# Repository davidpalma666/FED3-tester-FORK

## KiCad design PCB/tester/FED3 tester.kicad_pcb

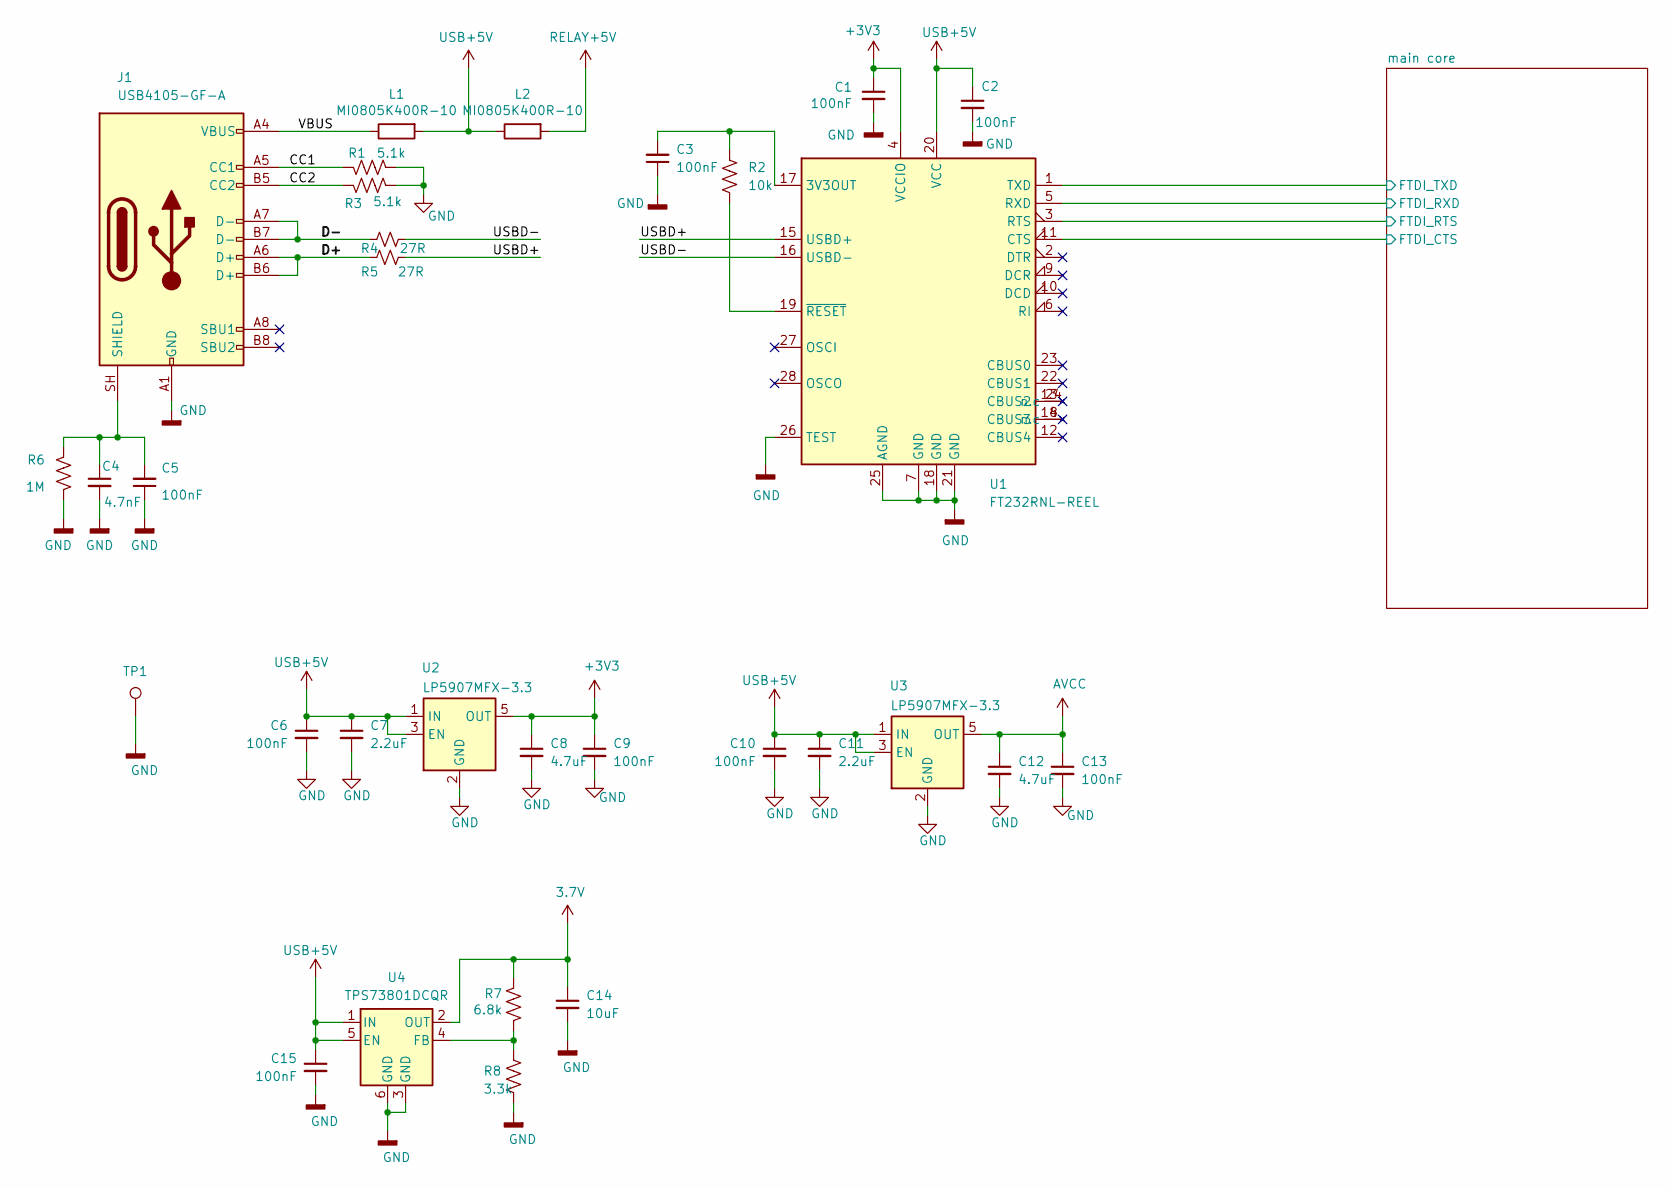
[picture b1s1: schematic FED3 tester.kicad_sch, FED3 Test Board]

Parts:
C1, C2, C3, C5, C6, C9, C10, C13, C15: 100nF; C_0402_1005Metric; Tolerance 10%; Voltage 50V; MPN CGA2B3X7R1H104K050BB
C4: 4.7nF; C_0402_1005Metric; Tolerance 10%; Voltage 100V; MPN 885012205084
C7, C11: 2.2uF; C_0603_1608Metric; Tolerance 10%; Voltage 25V; MPN GRM188R61E225KA12D
C8, C12: 4.7uF; C_0603_1608Metric; Tolerance 10%; Voltage 16V; MPN C1608X6S1C475K080AC
C14: 10uF; C_1206_3216Metric; Tolerance 10%; Voltage 25V; MPN GRM31CR71E106KA12L
J1: USB4105-GF-A; USB_C_Receptacle_GCT_USB4105-xx-A_16P_TopMnt_Horizontal; MPN USB4105-GF-A
L1, L2: MI0805K400R-10; R_0805_2012Metric; MPN MI0805K400R-10
R1, R3: 5.1k; R_0402_1005Metric; Tolerance 0.1%; MPN RT0402BRD075K1L
R2: 10k; R_0402_1005Metric; Tolerance 0.1%; MPN CPF0402B10KE1
R4, R5: 27R; R_0402_1005Metric; Tolerance 1%; MPN RMCF0402FT27R0
R6: 1M; R_0402_1005Metric; Tolerance 1%; MPN CRCW04021M00FKED
R7: 6.8k; R_0402_1005Metric; Tolerance 1%; MPN RC0402FR-076K8L
R8: 3.3k; R_0402_1005Metric; Tolerance 1%; MPN ERJ-2RKF3301X
TP1: GND; PinHeader_1x01_P2.54mm_Vertical; MPN n.a
U1: FT232RNL-REEL; SSOP-28_5.3x10.2mm_P0.65mm; MPN FT232RNL-REEL
U2, U3: LP5907MFX-3.3; SOT-23-5; MPN LP5907MFX-3.3/NOPB
U4: TPS73801DCQR; SOT-223-6; MPN TPS73801DCQR

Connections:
3.7V: C14.1, R7.2, U4.2 (OUT); also elsewhere on the board
+3V3: C1.1, C8.1, C9.1, U1.4 (VCCIO), U2.5 (OUT); also elsewhere on the board
/CC1: J1.A5 (CC1), R1.1
/CC2: J1.B5 (CC2), R3.1
/D+: J1.A6 (D+), J1.B6 (D+), R5.2
/D-: J1.A7 (D-), J1.B7 (D-), R4.2
/USBD+: R5.1, U1.15 (USBD+)
/USBD-: R4.1, U1.16 (USBD-)
/VBUS: J1.A4 (VBUS), J1.A9 (VBUS), J1.B4 (VBUS), J1.B9 (VBUS), L1.1
/main core/FTDI_CTS: U1.11 (CTS); also elsewhere on the board
/main core/FTDI_RTS: U1.3 (RTS); also elsewhere on the board
/main core/FTDI_RXD: U1.5 (RXD); also elsewhere on the board
/main core/FTDI_TXD: U1.1 (TXD); also elsewhere on the board
AVCC: C12.1, C13.1, U3.5 (OUT); also elsewhere on the board
GND: C1.2, C2.2, C3.1, C4.2, C5.1, C6.2, C7.2, C8.2, C9.2, C10.2, C11.2, C12.2, C13.2, C14.2, C15.2, J1.A1 (GND), J1.A12 (GND), J1.B1 (GND), J1.B12 (GND), R1.2, R3.2, R6.1, R8.1, TP1.1 (1_1), U1.7 (GND), U1.18 (GND), U1.21 (GND), U1.25 (AGND), U1.26 (TEST), U2.2 (GND), U3.2 (GND), U4.3 (GND), U4.6 (GND); also elsewhere on the board
unnamed: C4.1, C5.2, J1.SH (SHIELD), R6.2
unnamed: C3.2, R2.1, U1.17 (3V3OUT)
unnamed: R2.2, U1.19 (~RESET)
unnamed: R7.1, R8.2, U4.4 (FB)
RELAY+5V: L2.2; also elsewhere on the board
USB+5V: C2.1, C6.1, C7.1, C10.1, C11.1, C15.1, L1.2, L2.1, U1.20 (VCC), U2.1 (IN), U2.3 (EN), U3.1 (IN), U3.3 (EN), U4.1 (IN), U4.5 (EN); also elsewhere on the board

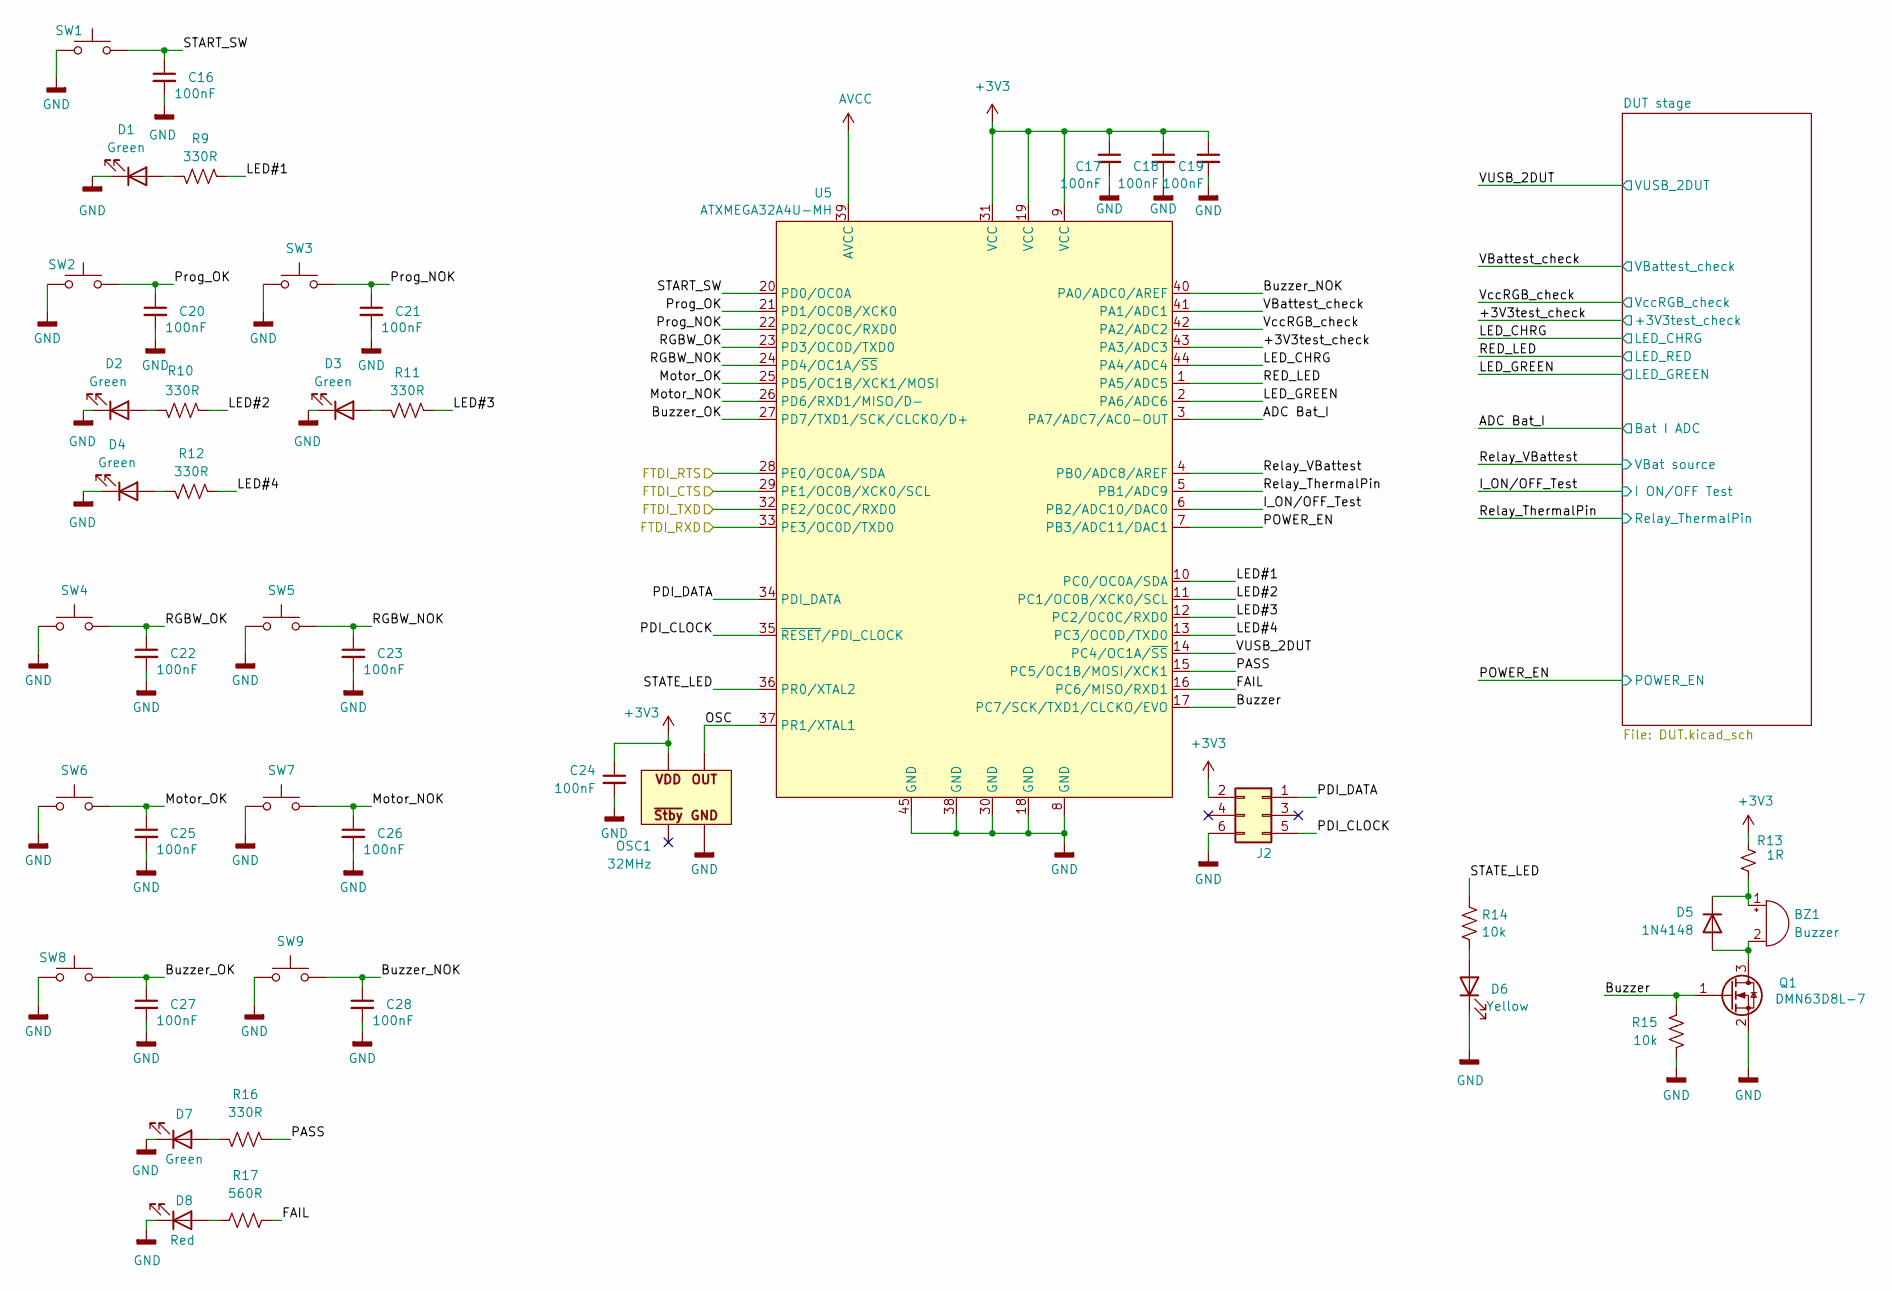
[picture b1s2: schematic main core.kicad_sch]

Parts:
BZ1: Buzzer; SMT-0540-T-9-R Buzzer; Voltage 3V; MPN CSS-0575A-SMT-TR
C16, C17, C18, C19, C20, C21, C22, C23, C24, C25, C26, C27, C28: 100nF; C_0402_1005Metric; Tolerance 10%; Voltage 50V; MPN CGA2B3X7R1H104K050BB
D1, D2, D3, D4, D7: Green; LED_0603_1608Metric; MPN LTST-C191KGKT
D5: 1N4148; D_SOD-123; MPN 1N4148WS-E3-18
D6: Yellow; LED_0603_1608Metric; MPN 5990040007F
D8: Red; LED_0603_1608Metric; MPN 5990010007F
J2: PR20203VBDN; PinHeader_2x03_P2.54mm_Vertical; MPN PR20203VBDN
OSC1: 32MHz; OSC; MPN DSC1001CI5-032.0000
Q1: DMN63D8L-7; SOT-23; MPN DMN63D8L-7
R9, R10, R11, R12, R16: 330R; R_0402_1005Metric; Tolerance 1%; MPN CRCW0402330RFKEDHP
R13: 1R; R_0402_1005Metric; Tolerance 1%; MPN CRCW04021R00FKEDC
R14, R15: 10k; R_0402_1005Metric; Tolerance 0.1%; MPN CPF0402B10KE1
R17: 560R; R_0402_1005Metric; Tolerance 1%; MPN CRCW0402560RFKED
SW1, SW2, SW3, SW4, SW5, SW6, SW7, SW8, SW9: TL3305BF260QG; SW_SPST_TL3305B; MPN TL3305BF260QG
U5: ATXMEGA32A4U-MH; QFN-44-1EP_7x7mm_P0.5mm_EP5.2x5.2mm; MPN ATXMEGA32A4U-MHR

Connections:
+3V3: C17.1, C18.1, C19.1, C24.1, J2.2, OSC1.4 (VDD), R13.1, U5.9 (VCC), U5.19 (VCC), U5.31 (VCC); also elsewhere on the board
/main core/+3V3test_check: U5.43 (PA3/ADC3); also elsewhere on the board
/main core/ADC Bat_I: U5.3 (PA7/ADC7/AC0-OUT); also elsewhere on the board
/main core/Buzzer: Q1.1 (G), R15.2, U5.17 (PC7/SCK/TXD1/CLCKO/EVO)
/main core/Buzzer_NOK: C28.1, SW9.2, U5.40 (PA0/ADC0/AREF)
/main core/Buzzer_OK: C27.1, SW8.2, U5.27 (PD7/TXD1/SCK/CLCKO/D+)
/main core/FAIL: R17.2, U5.16 (PC6/MISO/RXD1)
/main core/FTDI_CTS: U5.29 (PE1/OC0B/XCK0/SCL); also elsewhere on the board
/main core/FTDI_RTS: U5.28 (PE0/OC0A/SDA); also elsewhere on the board
/main core/FTDI_RXD: U5.33 (PE3/OC0D/TXD0); also elsewhere on the board
/main core/FTDI_TXD: U5.32 (PE2/OC0C/RXD0); also elsewhere on the board
/main core/I_ON/OFF_Test: U5.6 (PB2/ADC10/DAC0); also elsewhere on the board
/main core/LED#1: R9.2, U5.10 (PC0/OC0A/SDA)
/main core/LED#2: R10.2, U5.11 (PC1/OC0B/XCK0/SCL)
/main core/LED#3: R11.2, U5.12 (PC2/OC0C/RXD0)
/main core/LED#4: R12.2, U5.13 (PC3/OC0D/TXD0)
/main core/LED_CHRG: U5.44 (PA4/ADC4); also elsewhere on the board
/main core/LED_GREEN: U5.2 (PA6/ADC6); also elsewhere on the board
/main core/Motor_NOK: C26.1, SW7.2, U5.26 (PD6/RXD1/MISO/D-)
/main core/Motor_OK: C25.1, SW6.2, U5.25 (PD5/OC1B/XCK1/MOSI)
/main core/OSC: OSC1.3 (OUT), U5.37 (PR1/XTAL1)
/main core/PASS: R16.2, U5.15 (PC5/OC1B/MOSI/XCK1)
/main core/PDI_CLOCK: J2.5, U5.35 (~RESET/PDI_CLOCK)
/main core/PDI_DATA: J2.1, U5.34 (PDI_DATA)
/main core/POWER_EN: U5.7 (PB3/ADC11/DAC1); also elsewhere on the board
/main core/Prog_NOK: C21.1, SW3.2, U5.22 (PD2/OC0C/RXD0)
/main core/Prog_OK: C20.1, SW2.2, U5.21 (PD1/OC0B/XCK0)
/main core/RED_LED: U5.1 (PA5/ADC5); also elsewhere on the board
/main core/RGBW_NOK: C23.1, SW5.2, U5.24 (PD4/OC1A/~SS)
/main core/RGBW_OK: C22.1, SW4.2, U5.23 (PD3/OC0D/TXD0)
/main core/Relay_ThermalPin: U5.5 (PB1/ADC9); also elsewhere on the board
/main core/Relay_VBattest: U5.4 (PB0/ADC8/AREF); also elsewhere on the board
/main core/START_SW: C16.1, SW1.2, U5.20 (PD0/OC0A)
/main core/STATE_LED: R14.2, U5.36 (PR0/XTAL2)
/main core/VBattest_check: U5.41 (PA1/ADC1); also elsewhere on the board
/main core/VUSB_2DUT: U5.14 (PC4/OC1A/~SS); also elsewhere on the board
/main core/VccRGB_check: U5.42 (PA2/ADC2); also elsewhere on the board
AVCC: U5.39 (AVCC); also elsewhere on the board
GND: C16.2, C17.2, C18.2, C19.2, C20.2, C21.2, C22.2, C23.2, C24.2, C25.2, C26.2, C27.2, C28.2, D1.1 (K), D2.1 (K), D3.1 (K), D4.1 (K), D6.1 (K), D7.1 (K), D8.1 (K), J2.6, OSC1.2 (GND), Q1.2 (S), R15.1, SW1.1, SW2.1, SW3.1, SW4.1, SW5.1, SW6.1, SW7.1, SW8.1, SW9.1, U5.8 (GND), U5.18 (GND), U5.30 (GND), U5.38 (GND), U5.45 (GND); also elsewhere on the board
unnamed: BZ1.1 (+), D5.1 (K), R13.2
unnamed: BZ1.2 (-), D5.2 (A), Q1.3 (D)
unnamed: D1.2 (A), R9.1
unnamed: D2.2 (A), R10.1
unnamed: D3.2 (A), R11.1
unnamed: D4.2 (A), R12.1
unnamed: D6.2 (A), R14.1
unnamed: D7.2 (A), R16.1
unnamed: D8.2 (A), R17.1

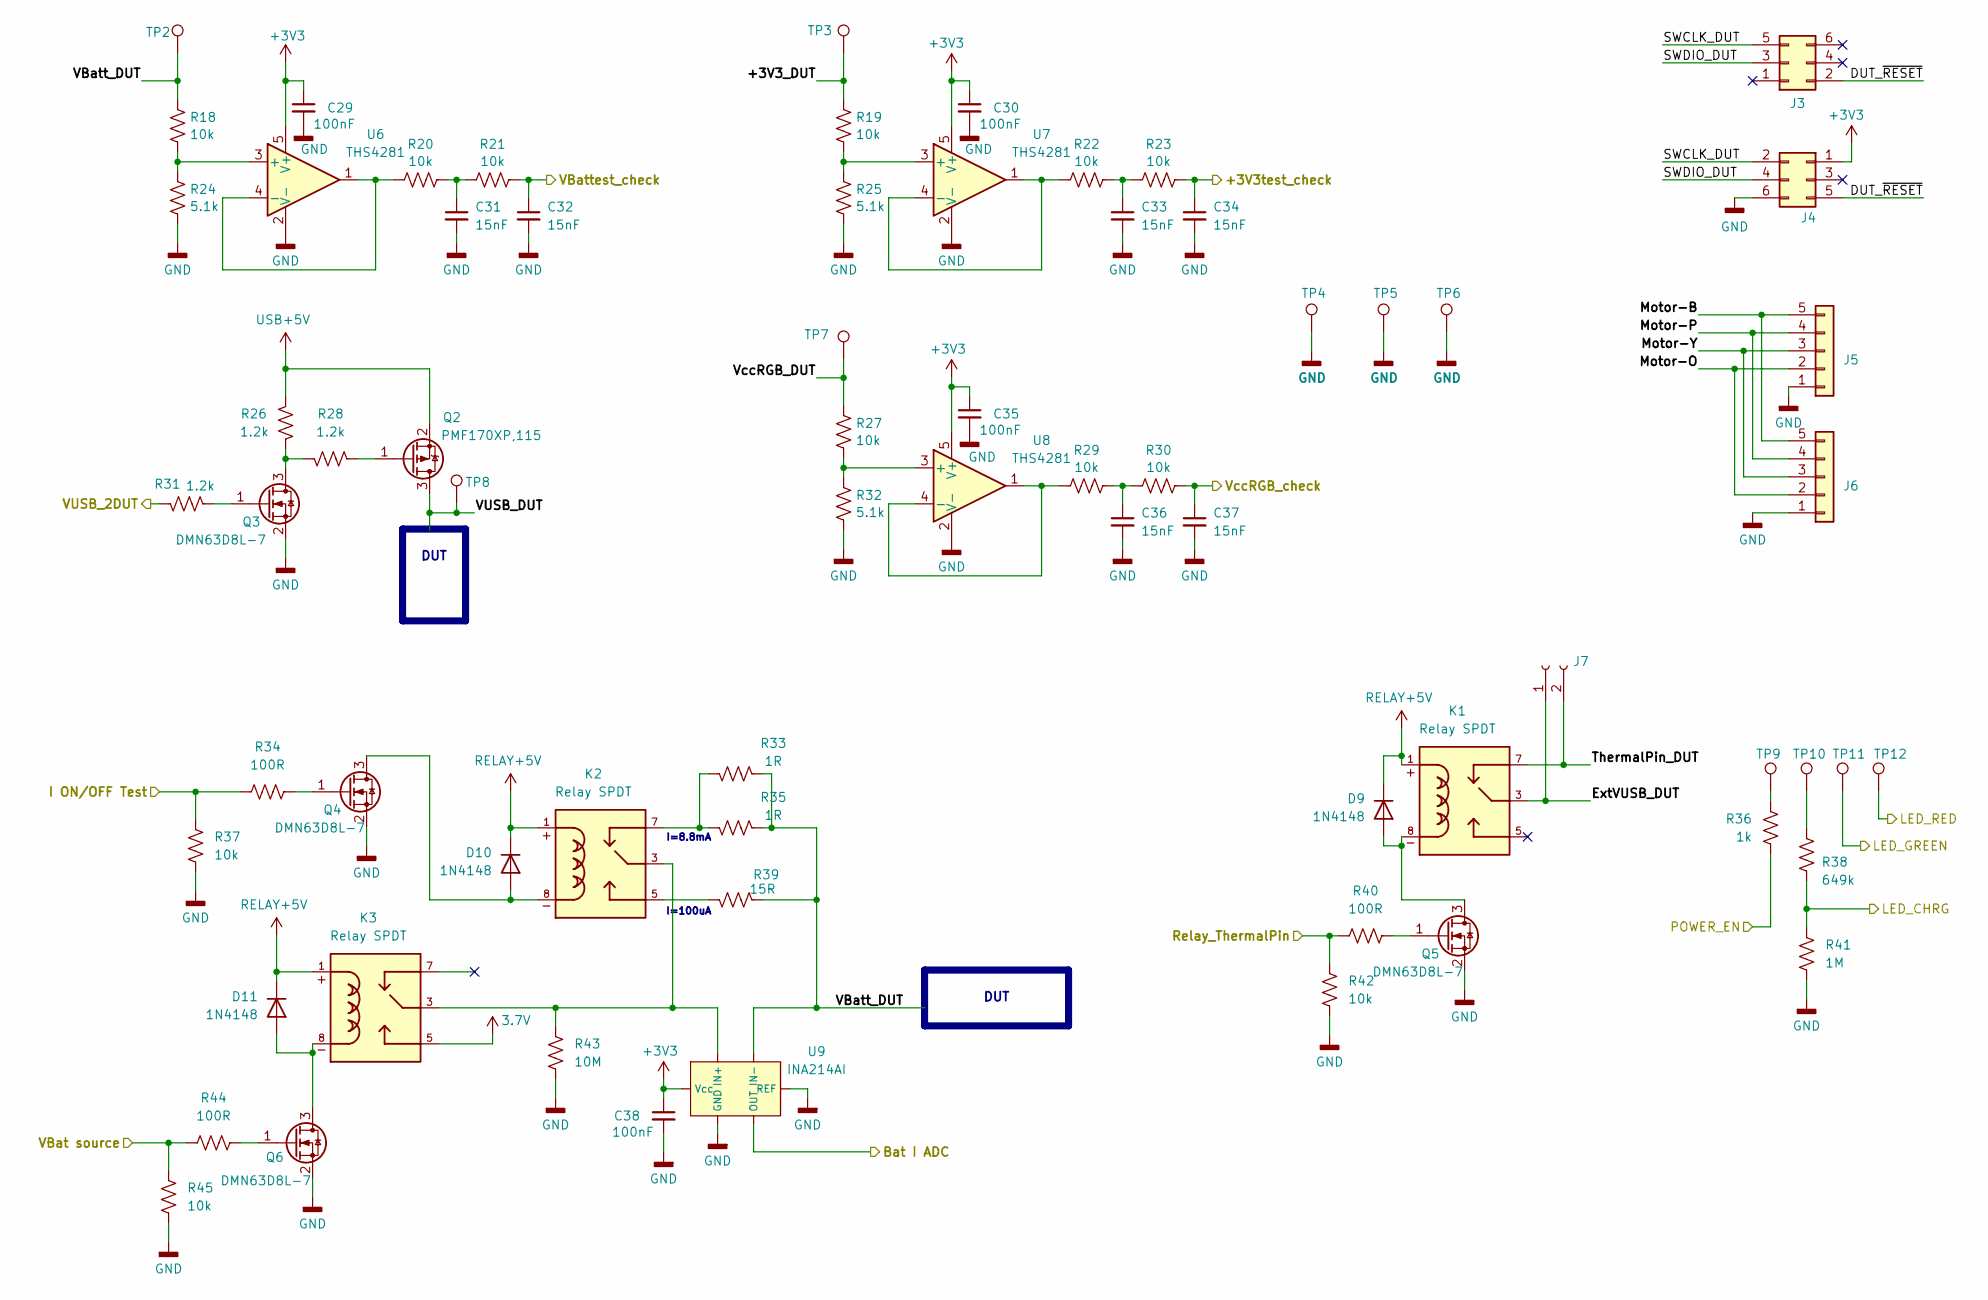
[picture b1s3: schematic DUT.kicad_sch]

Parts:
C29, C30, C35, C38: 100nF; C_0402_1005Metric; Tolerance 10%; Voltage 50V; MPN CGA2B3X7R1H104K050BB
C31, C32, C33, C34, C36, C37: 15nF; C_0402_1005Metric; Tolerance 10%; Voltage 35V; MPN CGA2B3X7R1V153K050BB
D9, D10, D11: 1N4148; D_SOD-123; MPN 1N4148WS-E3-18
J3: 6pin_hd; PinHeader_2x03_to Probes; MPN n.a
J4: 61300621021; PinHeader_2x03_P2.54mm_Horizontal; MPN 61300621021
J5: PPTC051LFBN-RC; PinSocket_1x05_P2.54mm_Vertical; MPN PPTC051LFBN-RC
J6: 61300511021; PinSocket_1x05_P2.54mm_Horizontal; MPN 61300511021
J7: PPTC021LFBN-RC; PinSocket_1x02_P2.54mm_Vertical; MPN PPTC021LFBN-RC
K1, K2, K3: Relay SPDT; RELAY_1462042-8; MPN 1462042-8
Q2: PMF170XP,115; SOT-323_SC-70; MPN PMF170XP,115
Q3, Q4, Q5, Q6: DMN63D8L-7; SOT-23; MPN DMN63D8L-7
R18, R19, R20, R21, R22, R23, R27, R29, R30, R37, R42, R45: 10k; R_0402_1005Metric; Tolerance 0.1%; MPN CPF0402B10KE1
R24, R25, R32: 5.1k; R_0402_1005Metric; Tolerance 0.1%; MPN RT0402BRD075K1L
R26, R28, R31: 1.2k; R_0402_1005Metric; Tolerance 0.1%; MPN ERA-2AEB122X
R33, R35: 1R; R_0603_1608Metric; Tolerance 0.1%; MPN RT0603BRD071RL
R34, R40, R44: 100R; R_0402_1005Metric; Tolerance 1%; MPN RCS0402100RFKED
R36: 1k; R_0402_1005Metric; Tolerance 1%; MPN CRCW04021K00FKED
R38: 649k; R_0402_1005Metric; Tolerance 1%; MPN ERJ-2RKF6493X
R39: 15R; R_1206_3216Metric; Tolerance 0.1%; MPN PHPA1206E15R0BST1
R41: 1M; R_0402_1005Metric; Tolerance 1%; MPN CRCW04021M00FKED
R43: 10M; R_0402_1005Metric; Tolerance 1%; MPN CRCW040210M0FKED
TP2: VBattest; Pin_D1.75mm; MPN n.a
TP3: +3V3test; Pin_D1.75mm; MPN n.a
TP4, TP5, TP6, TP9, TP10, TP11, TP12: GND; Pin_D1.75mm; MPN n.a
TP7: VccRGB; Pin_D1.75mm; MPN n.a
TP8: VUSBtest; Pin_D1.75mm; MPN n.a
U6, U7, U8: THS4281; SOT-23-5; MPN THS4281DBVT
U9: INA214AI; SOT-363_SC-70-6; MPN INA214AIDCKR

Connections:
3.7V: K3.5; also elsewhere on the board
+3V3: C29.1, C30.1, C35.1, C38.1, J4.1, U6.5 (V+), U7.5 (V+), U8.5 (V+), U9.3 (Vcc); also elsewhere on the board
/main core/+3V3test_check: C34.1, R23.2; also elsewhere on the board
/main core/ADC Bat_I: U9.6 (OUT); also elsewhere on the board
/main core/DUT stage/+3V3_DUT: R19.2, TP3.1 (1_1)
/main core/DUT stage/DUT_~RESET: J3.2, J4.5
/main core/DUT stage/ExtVUSB_DUT: J7.1, K1.3
/main core/DUT stage/Motor-B: J5.5, J6.5
/main core/DUT stage/Motor-O: J5.2, J6.2
/main core/DUT stage/Motor-P: J5.4, J6.4
/main core/DUT stage/Motor-Y: J5.3, J6.3
/main core/DUT stage/SWCLK_DUT: J3.5, J4.2
/main core/DUT stage/SWDIO_DUT: J3.3, J4.4
/main core/DUT stage/ThermalPin_DUT: J7.2, K1.7
/main core/DUT stage/VBatt_DUT: R18.2, R33.2, R35.2, R39.1, TP2.1 (1_1), U9.5 (IN-)
/main core/DUT stage/VUSB_DUT: Q2.3 (D), TP8.1 (1_1)
/main core/DUT stage/VccRGB_DUT: R27.2, TP7.1 (1_1)
/main core/I_ON/OFF_Test: R34.1, R37.2; also elsewhere on the board
/main core/LED_CHRG: R38.1, R41.2; also elsewhere on the board
/main core/LED_GREEN: TP11.1 (1_1); also elsewhere on the board
/main core/POWER_EN: R36.1; also elsewhere on the board
/main core/RED_LED: TP12.1 (1_1); also elsewhere on the board
/main core/Relay_ThermalPin: R40.1, R42.2; also elsewhere on the board
/main core/Relay_VBattest: R44.1, R45.2; also elsewhere on the board
/main core/VBattest_check: C32.1, R21.2; also elsewhere on the board
/main core/VUSB_2DUT: R31.2; also elsewhere on the board
/main core/VccRGB_check: C37.1, R30.2; also elsewhere on the board
GND: C29.2, C30.2, C31.2, C32.2, C33.2, C34.2, C35.2, C36.2, C37.2, C38.2, J4.6, J5.1, J6.1, Q3.2 (S), Q4.2 (S), Q5.2 (S), Q6.2 (S), R24.1, R25.1, R32.1, R37.1, R41.1, R42.1, R43.1, R45.1, TP4.1 (1_1), TP5.1 (1_1), TP6.1 (1_1), U6.2 (V-), U7.2 (V-), U8.2 (V-), U9.1 (REF), U9.2 (GND); also elsewhere on the board
unnamed: C31.1, R20.2, R21.1
unnamed: C33.1, R22.2, R23.1
unnamed: C36.1, R29.2, R30.1
unnamed: D9.2 (A), K1.8, Q5.3 (D)
unnamed: D10.2 (A), K2.8, Q4.3 (D)
unnamed: D11.2 (A), K3.8, Q6.3 (D)
unnamed: K2.5, R39.2
unnamed: K2.7, R33.1, R35.1
unnamed: Q2.1 (G), R28.2
unnamed: Q3.3 (D), R26.1, R28.1
unnamed: Q3.1 (G), R31.1
unnamed: Q4.1 (G), R34.2
unnamed: Q5.1 (G), R40.2
unnamed: Q6.1 (G), R44.2
unnamed: R36.2, TP9.1 (1_1)
unnamed: R38.2, TP10.1 (1_1)
unnamed: R18.1, R24.2, U6.3 (+)
unnamed: R20.1, U6.1, U6.4 (-)
unnamed: R19.1, R25.2, U7.3 (+)
unnamed: R22.1, U7.1, U7.4 (-)
unnamed: R27.1, R32.2, U8.3 (+)
unnamed: R29.1, U8.1, U8.4 (-)
unnamed: K2.3, K3.3, R43.2, U9.4 (IN+)
RELAY+5V: D9.1 (K), D10.1 (K), D11.1 (K), K1.1, K2.1, K3.1; also elsewhere on the board
USB+5V: Q2.2 (S), R26.2; also elsewhere on the board

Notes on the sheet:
I=100uA
I=8.8mA
DUT

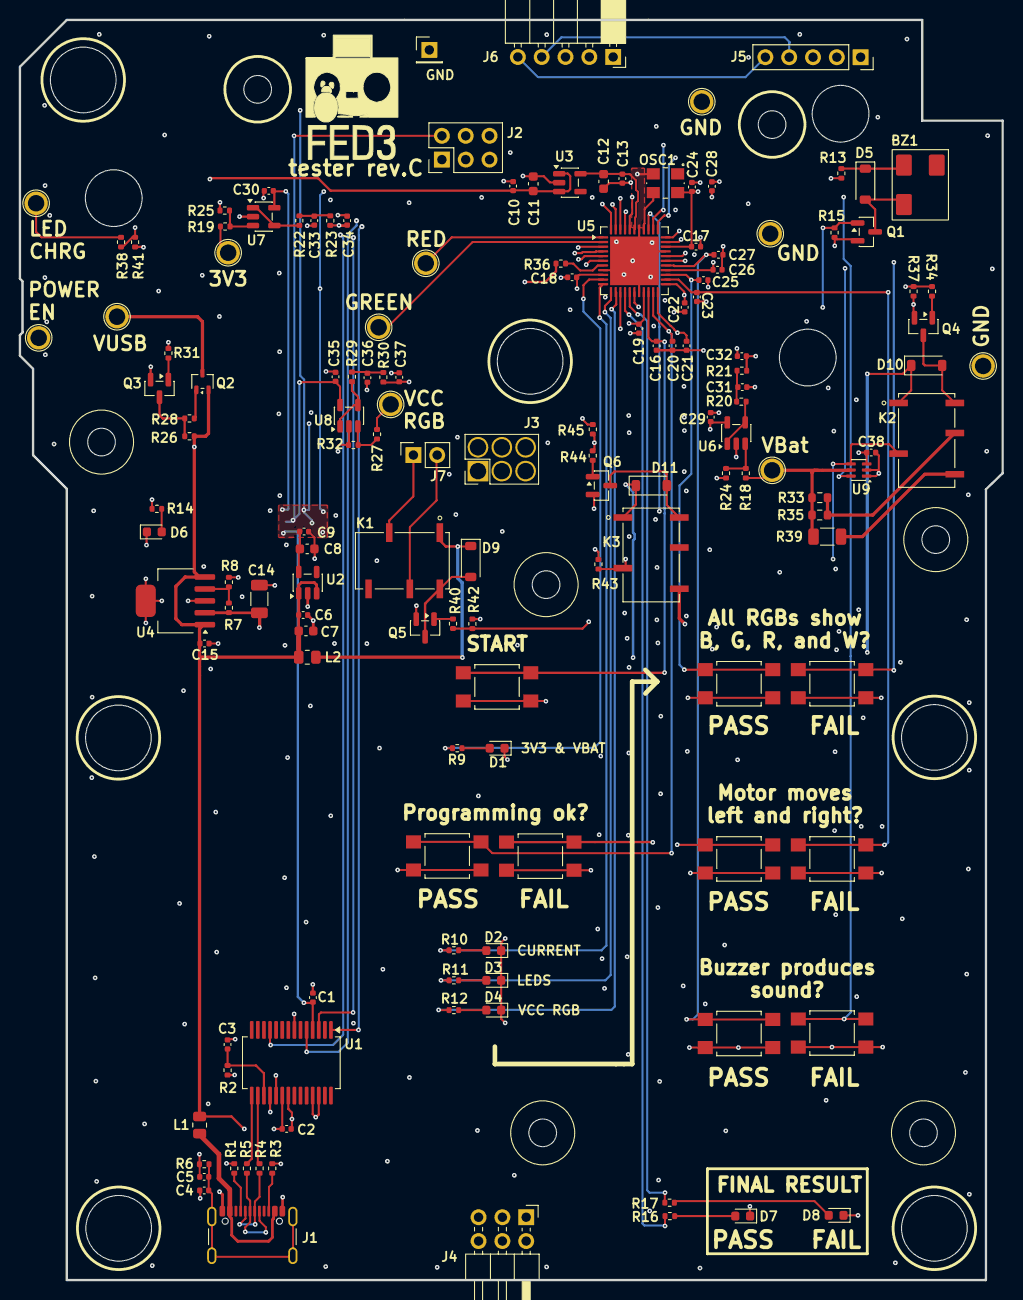
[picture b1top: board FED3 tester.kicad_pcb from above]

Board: 4 copper layers, 104.8 x 134.4 mm, 152 parts (0 on the bottom side), 98 nets.

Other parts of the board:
@HOLE6, @HOLE6#2, @HOLE6#3: MechHole_6.05mm
Ref**: Val**; MechHole_2.95mm
Ref**#2, Ref**#3, Ref**#4, Ref**#5: Val**; MechHole_2.95mm

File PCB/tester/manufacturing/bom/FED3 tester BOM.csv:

"#","Qty","Reference","Value","Tolerance","Footprint","TempCo","Voltage","DNP","OEPSPN","MPN"
"1","1","BZ1","Buzzer","","FED3_PCBLib:SMT-0540-T-9-R Buzzer","","3V","","OEPS100079","CSS-0575A-SMT-TR"
"2","26","C1,C2,C3,C5,C6,C9,C10,C13,C15,C16,C17,C18,C19,C20,C21,C22,C23,C24,C25,C26,C27,C28,C29,C30,C35,C38","100nF","10%","Capacitor_SMD:C_0402_1005Metric","X7R","50V","","OEPS010016","CGA2B3X7R1H104K050BB"
"3","1","C4","4.7nF","10%","Capacitor_SMD:C_0402_1005Metric","X7R","100V","","OEPS010017","885012205084"
"4","2","C7,C11","2.2uF","10%","Capacitor_SMD:C_0603_1608Metric","X5R","25V","","OEPS010075","GRM188R61E225KA12D"
"5","2","C8,C12","4.7uF","10%","Capacitor_SMD:C_0603_1608Metric","X6S","16V","","OEPS010018","C1608X6S1C475K080AC"
"6","1","C14","10uF","10%","Capacitor_SMD:C_1206_3216Metric","X7R","25V","","OEPS010007","GRM31CR71E106KA12L"
"7","6","C31,C32,C33,C34,C36,C37","15nF","10%","Capacitor_SMD:C_0402_1005Metric","X7R","35V","","OEPS010023","CGA2B3X7R1V153K050BB"
"8","5","D1,D2,D3,D4,D7","Green","","LED_SMD:LED_0603_1608Metric","","","","OEPS030005","LTST-C191KGKT"
"9","4","D5,D9,D10,D11","1N4148","","Diode_SMD:D_SOD-123","","","","OEPS030052","1N4148WS-E3-18"
"10","1","D6","Yellow","","LED_SMD:LED_0603_1608Metric","","","","OEPS030043","5990040007F"
"11","1","D8","Red","","LED_SMD:LED_0603_1608Metric","","","","OEPS030044","5990010007F"
"12","1","J1","USB4105-GF-A","","Connector_USB:USB_C_Receptacle_GCT_USB4105-xx-A_16P_TopMnt_Horizontal","","","","OEPS070105","USB4105-GF-A"
"13","1","J2","PR20203VBDN","","Connector_PinHeader_2.54mm:PinHeader_2x03_P2.54mm_Vertical","","","","OEPS070124","PR20203VBDN"
"14","1","J4","61300621021","","Connector_PinHeader_2.54mm:PinHeader_2x03_P2.54mm_Horizontal","","","","OEPS070144","61300621021"
"15","1","J5","PPTC051LFBN-RC","","Connector_PinSocket_2.54mm:PinSocket_1x05_P2.54mm_Vertical","","","","OEPS070142","PPTC051LFBN-RC"
"16","1","J6","61300511021","","Connector_PinSocket_2.54mm:PinSocket_1x05_P2.54mm_Horizontal","","","","OEPS070143","61300511021"
"17","1","J7","PPTC021LFBN-RC","","Connector_PinSocket_2.54mm:PinSocket_1x02_P2.54mm_Vertical","","","","OEPS070095","PPTC021LFBN-RC"
"18","3","K1,K2,K3","Relay SPDT","","FED3_PCBLib:RELAY_1462042-8","","","","OEPS100078","1462042-8"
"19","2","L1,L2","MI0805K400R-10","","Resistor_SMD:R_0805_2012Metric","","","","OEPS040003","MI0805K400R-10"
"20","1","OSC1","32MHz","","FED3_PCBLib:OSC","","","","OEPS080018","DSC1001CI5-032.0000"
"21","5","Q1,Q3,Q4,Q5,Q6","DMN63D8L-7","","Package_TO_SOT_SMD:SOT-23","","","","OEPS060013","DMN63D8L-7"
"22","1","Q2","PMF170XP,115","","Package_TO_SOT_SMD:SOT-323_SC-70","","","","OEPS060012","PMF170XP,115"
"23","5","R1,R3,R24,R25,R32","5.1k","0.1%","Resistor_SMD:R_0402_1005Metric","","","","OEPS020203","RT0402BRD075K1L"
"24","15","R2,R14,R15,R18,R19,R20,R21,R22,R23,R27,R29,R30,R37,R42,R45","10k","0.1%","Resistor_SMD:R_0402_1005Metric","","","","OEPS020043","CPF0402B10KE1"
"25","2","R4,R5","27R","1%","Resistor_SMD:R_0402_1005Metric","","","","OEPS020170","RMCF0402FT27R0"
"26","2","R6,R41","1M","1%","Resistor_SMD:R_0402_1005Metric","","","","OEPS020026","CRCW04021M00FKED"
"27","1","R7","6.8k","1%","Resistor_SMD:R_0402_1005Metric","","","","OEPS020242","RC0402FR-076K8L"
"28","1","R8","3.3k","1%","Resistor_SMD:R_0402_1005Metric","","","","OEPS020083","ERJ-2RKF3301X"
"29","5","R9,R10,R11,R12,R16","330R","1%","Resistor_SMD:R_0402_1005Metric","","","","OEPS020191","CRCW0402330RFKEDHP "
"30","1","R13","1R","1%","Resistor_SMD:R_0402_1005Metric","","","","OEPS020061","CRCW04021R00FKEDC"
"31","1","R17","560R","1%","Resistor_SMD:R_0402_1005Metric","","","","OEPS020193","CRCW0402560RFKED"
"32","3","R26,R28,R31","1.2k","0.1%","Resistor_SMD:R_0402_1005Metric","","","","OEPS020213","ERA-2AEB122X"
"33","2","R33,R35","1R","0.1%","Resistor_SMD:R_0603_1608Metric","","","","OEPS020243","RT0603BRD071RL"
"34","3","R34,R40,R44","100R","1%","Resistor_SMD:R_0402_1005Metric","","","","OEPS020028","RCS0402100RFKED"
"35","1","R36","1k","1%","Resistor_SMD:R_0402_1005Metric","","","","OEPS020027","CRCW04021K00FKED"
"36","1","R38","649k","1%","Resistor_SMD:R_0402_1005Metric","","","","OEPS020022","ERJ-2RKF6493X"
"37","1","R39","15R","0.1%","Resistor_SMD:R_1206_3216Metric","","","","OEPS020244","PHPA1206E15R0BST1"
"38","1","R43","10M","1%","Resistor_SMD:R_0402_1005Metric","","","","OEPS020211","CRCW040210M0FKED"
"39","9","SW1,SW2,SW3,SW4,SW5,SW6,SW7,SW8,SW9","TL3305BF260QG","","Button_Switch_SMD:SW_SPST_TL3305B","","","","OEPS100061","TL3305BF260QG"
"40","1","U1","FT232RNL-REEL","","Package_SO:SSOP-28_5.3x10.2mm_P0.65mm","","","","OEPS080093","FT232RNL-REEL"
"41","2","U2,U3","LP5907MFX-3.3","","Package_TO_SOT_SMD:SOT-23-5","","","","OEPS080016","LP5907MFX-3.3/NOPB"
"42","1","U4","TPS73801DCQR","","Package_TO_SOT_SMD:SOT-223-6","","","","OEPS080085","TPS73801DCQR"
"43","1","U5","ATXMEGA32A4U-MH","","Package_DFN_QFN:QFN-44-1EP_7x7mm_P0.5mm_EP5.2x5.2mm","","","","OEPS080116","ATXMEGA32A4U-MHR"
"44","3","U6,U7,U8","THS4281","","Package_TO_SOT_SMD:SOT-23-5","","","","OEPS080038","THS4281DBVT"
"45","1","U9","INA214AI","","Package_TO_SOT_SMD:SOT-363_SC-70-6","","","","OEPS080234","INA214AIDCKR"

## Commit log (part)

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2026-05-15 Red LED & decouplers
    - decoupler dos Switches mudados posição
    - LED vermelho & R_LED mudados valor/refª
2026-05-15 promenores componentes para a BOM
2026-05-18 sync with main
2026-06-12 início Rev.C
    - corrigido pinout dos relais
    - corrigido valor & MPN & OEPSPN de R13 =1R
    - feito re-routing: DRC=0
    - gerados ficheiros de produção
    - BOM actualizada
2026-06-15 actualizado ficheiro notas
